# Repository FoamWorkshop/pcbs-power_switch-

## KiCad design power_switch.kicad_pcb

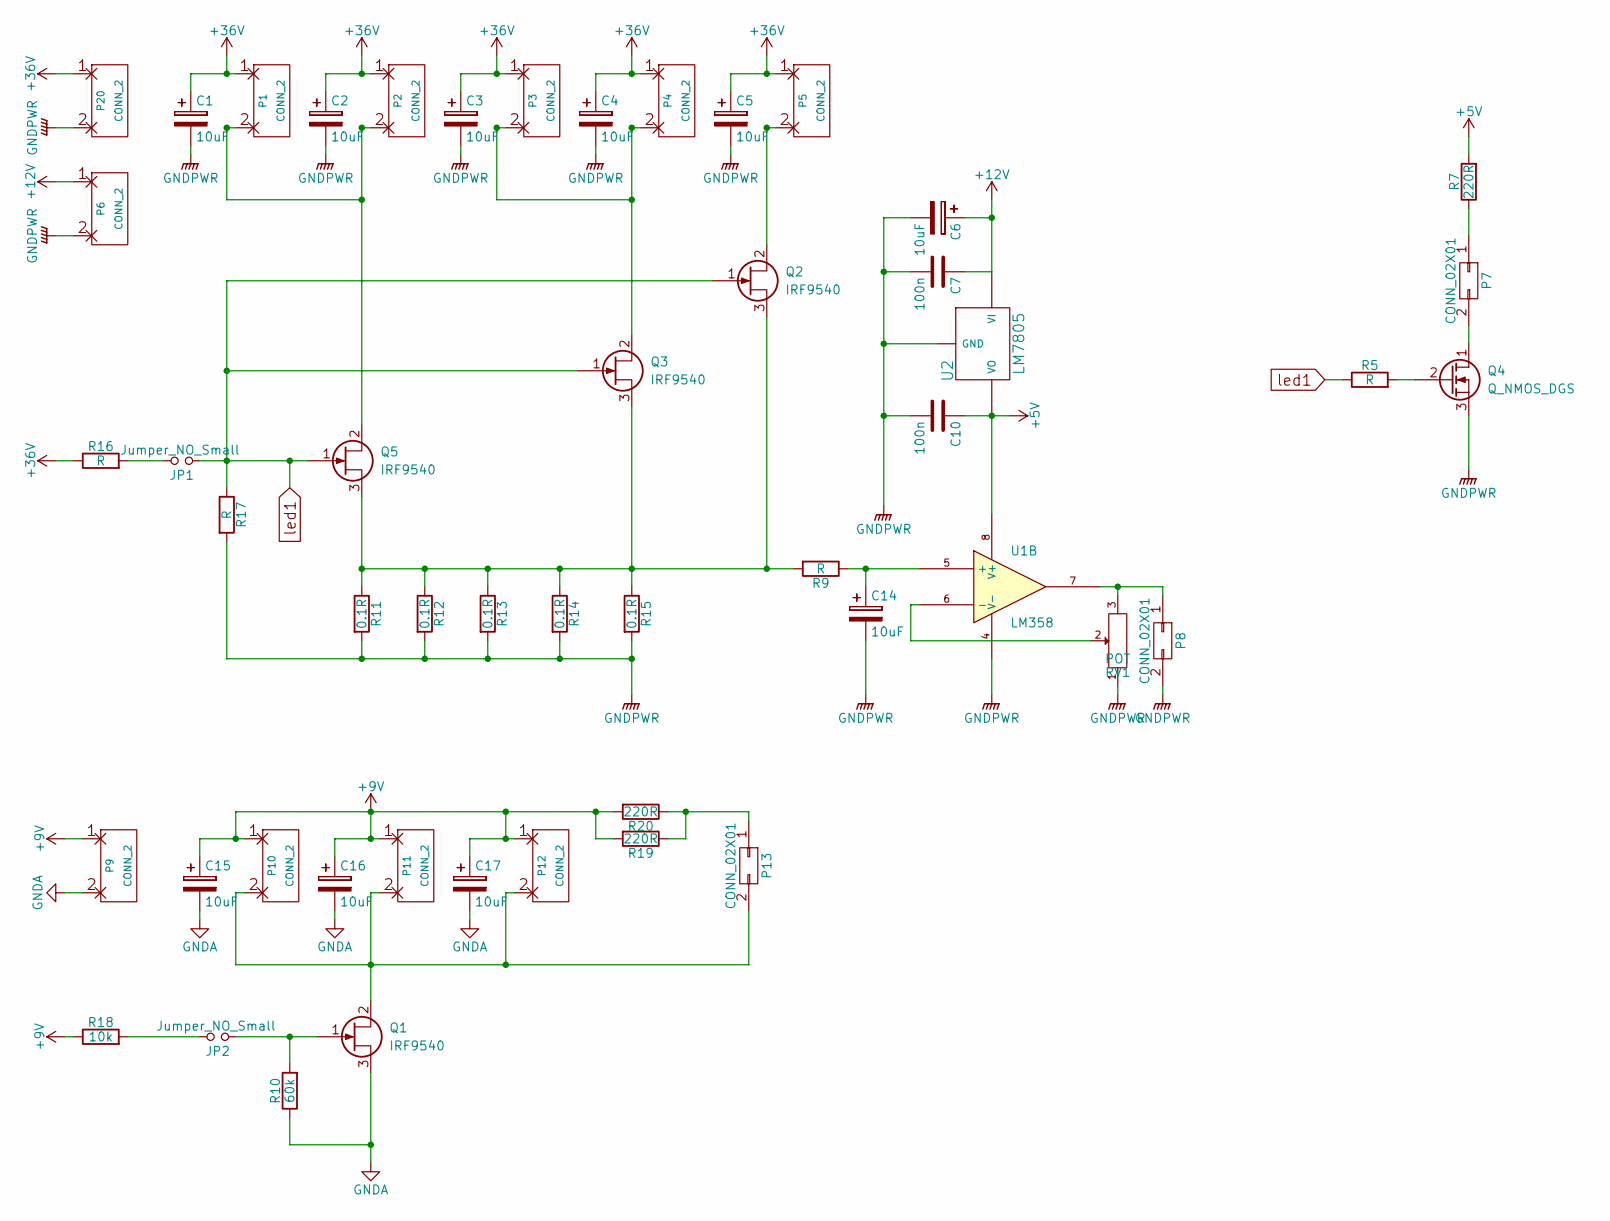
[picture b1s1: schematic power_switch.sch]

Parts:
C1, C2, C3, C4, C5: 10uF; Elko_vert_20x10mm_RM5
C6, C14: 10uF; Elko_vert_11.2x6.3mm_RM2.5
C7, C10: 100n; C_Disc_D3_P2.5
C15, C16, C17: 10uF; C_Radial_D8_L11.5_P3.5
JP1, JP2: Jumper_NO_Small; Pin_Header_Straight_1x02_Pitch2.54mm
P1, P2, P3, P4, P5, P6, P9, P10, P11, P12, P20: CONN_2; bornier2_V
P7, P8, P13: CONN_02X01; Socket_Strip_Straight_2x01
Q1, Q2, Q3, Q5: IRF9540; TO-220_Neutral123_Vertical_LargePads_wide
Q4: Q_NMOS_DGS; TO-92_Inline_Narrow_Oval
R5, R9, R16, R17: R; R_Axial_DIN0207_L6.3mm_D2.5mm_P7.62mm_Horizontal
R7, R19, R20: 220R; R_Axial_DIN0207_L6.3mm_D2.5mm_P7.62mm_Horizontal
R10: 60k; R_Axial_DIN0207_L6.3mm_D2.5mm_P7.62mm_Horizontal
R11, R12, R13, R14, R15: 0.1R; Resistor_Cement_KOA-BGR-3N
R18: 10k; R_Axial_DIN0207_L6.3mm_D2.5mm_P7.62mm_Horizontal
RV1: POT; Potentiometer_Bourns_3296W_3-8Zoll_Inline_ScrewUp
U1: LM358; DIP-8_W7.62mm_LongPads
U2: LM7805; TO-220_L78XX

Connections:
+5V: C10.1, R7.2, U1.8 (V+), U2.VO
+9V: C15.1, C16.1, C17.1, P9.1, P10.1, P11.1, P12.1, R18.1, R19.2, R20.2
+12V: C6.1, C7.1, P6.1, U2.VI
+36V: C1.1, C2.1, C3.1, C4.1, C5.1, P1.1, P2.1, P3.1, P4.1, P5.1, P20.1, R16.1
GNDA: C15.2, C16.2, C17.2, P9.2, Q1.3 (S), R10.1
GNDPWR: C1.2, C2.2, C3.2, C4.2, C5.2, C6.2, C7.2, C10.2, C14.2, P6.2, P8.2, P20.2, Q4.3 (S), R11.2, R12.2, R13.2, R14.2, R15.2, R17.2, RV1.1, U1.4 (V-), U2.GND
unnamed: C14.1, R9.1, U1.5 (+)
unnamed: JP1.2, R16.2
unnamed: JP2.1, Q1.1 (G), R10.2
unnamed: JP2.2, R18.2
unnamed: P1.2, P2.2, Q5.2 (D)
unnamed: P3.2, P4.2, Q3.2 (D)
unnamed: P5.2, Q2.2 (D)
unnamed: P7.1, R7.1
unnamed: P7.2, Q4.1 (D)
unnamed: P8.1, RV1.3, U1.7
unnamed: P10.2, P11.2, P12.2, P13.2, Q1.2 (D)
unnamed: P13.1, R19.1, R20.1
unnamed: Q2.3 (S), Q3.3 (S), Q5.3 (S), R9.2, R11.1, R12.1, R13.1, R14.1, R15.1
unnamed: Q4.2 (G), R5.2
unnamed: RV1.2, U1.6 (-)
led1: JP1.1, Q2.1 (G), Q3.1 (G), Q5.1 (G), R5.1, R17.1

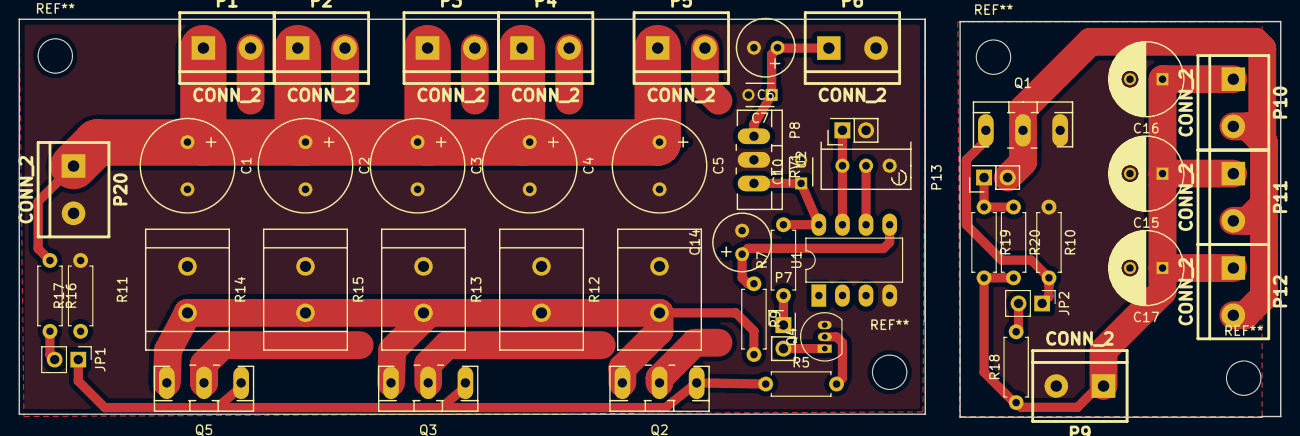
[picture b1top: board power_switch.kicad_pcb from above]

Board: 2 copper layers, 135.8 x 42.8 mm, 50 parts (0 on the bottom side), 22 nets.

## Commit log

2017-01-09 simplified version
2017-01-11 working simple switch - no base version removed
2017-01-11 shematic for power and logic circuit
2017-01-13 versin with buck converter for amp meter backup
2017-01-17 powerswitch with tracks
2017-01-17 added pcb file
2017-01-17 added gitignore
2017-01-19 corrected switching transistor pins order
